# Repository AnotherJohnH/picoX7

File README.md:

# picoX7

A software simulation of the Yamaha DX7 with a USB and physical MIDI interface for the Raspberry Pi Pico

Slightly boring [video](https://youtu.be/ZSuNV67vHK8) of the picoX7 playing the Yamaha DX7 ROM cartridge 1A patches...

## Status

Done...
   + I2S (via PIO) 16-bit stereo DAC interface at 49096 Hz
   + Use of the 2nd Arm Cortex-M, 8 voices per core
   + MIDI in support via UART and USB (including SYSEX in)
   + YM21280 OPS simulation (logarithmic)
   + YM21290 EGS simulation
   + Firmware simulation including pitch envelope, LFO, key sensitivity, level scaling, amplitude modulation
   + DX7 voice patches sounding close

To do...
   - Tune EGS simulation
   - Rate scaling
   - Portamento and glissando
   - Optimise to squeeze in more voices (?)

Limitations...
   - DAC implementation is quite different to the original. Dynamic range might be reduced?
   - Hitachi 6303 (~MC6803) CPU controller and firmware are not being emulated or fully simulated
   - 8 voices are on the left channel and 8 on the right ... stereo output needs to mixed to mono externally

Deviations/enhancements compared to a real DX7...
   + Each voice has it's own LFO
   + Each voice has it's own patch state (in theory when supported could load a different patch into each voice)
   + Support for 128 voice patches (DX7 had 32 internal and 32 cartridge)

See the [software blog](https://github.com/AnotherJohnH/picoX7/wiki/Software-Blog) and [hardware blog](https://github.com/AnotherJohnH/picoX7/wiki/Hardware-Blog)  for more detailed progress updates.

## Hardware

[Schematic](https://github.com/AnotherJohnH/Hardware/blob/main/picoX7/docs/schematic_v0.05.pdf) for the above.

For more information see [README](https://github.com/AnotherJohnH/Hardware/blob/main/picoX7/README.md) and the [hardware blog](https://github.com/AnotherJohnH/picoX7/wiki/Hardware-Blog)

The Pico is significantly overclocked to 191.08 MHz to support 16 voices and generate a jitter free sample rate of 49096 Hz.

RP2350 Picos as well as the older RP2040 Picos are supported.

## Software

### Checkout

This repo uses git sub-modules, so checkout using --recurse to clone all the
dependent source...

    git clone --recurse https://github.com/AnotherJohnH/picoX7.git

or

    git clone --recurse ssh://git@github.com/AnotherJohnH/picoX7.git

### Software dependencies

+ https://github.com/AnotherJohnH/Platform
+ arm-none-eabi-gcc
+ cmake via UNIX make or auto detection of ninja if installed
+ Python3
+ SDL2 (only for native test target)

### Build

Being developed on MacOS but should build on Linux too.

Indirect build of all supported targets, rpipico, rpipico2 and native with cmake and make (or ninja)...

    make

Build a single hardware target e.g. rpipico2 using cmake...

    mkdir build
    cd build
    cmake -DCMAKE_BUILD_TYPE=Release -DPLT_TARGET=rp2350 -DCMAKE_TOOLCHAIN_FILE=Platform/MTL/rp2350/target/toolchain.cmake ..
    make

flashable images will be found under the build sub-directory here...

    build/<target>/picoX7_RPIPIOC_I2S_DAC.uf2
    build/<target>/picoX7_RPIPIOC_PWM_DAC.uf2
    build/<target>/picoX7_RPIPIOC_PIMORONI_PICO_AUDIO.uf2
    build/<target>/picoX7_RPIPIOC_WAVESHARE_REV2_1.uf2
    build/<target>/picoX7_PIMORONI_VGA_DEMO.uf2

Build the native target...

    mkdir build
    cd build
    cmake -DCMAKE_BUILD_TYPE=Release -DPLT_TARGET=native ..
    make

a runable binary image will be found under the build subdirectory here...

    build/Source/picoX7_NATIVE

## License

This project is licensed under the MIT License - see the [LICENSE](LICENSE) file for details

## Acknowledgements

 + [Ken Shirriff](https://github.com/shirriff) for his very helpful series of [blogs](https://www.righto.com/2021/11/reverse-engineering-yamaha-dx7.html) reverse engineering the YM21280
 + [AJXS](https://github.com/ajxs) for their annotated [disassembly](https://ajxs.me/blog/Yamaha_DX7_Firmware_ROM_Disassembly.html) of the DX7 firmware ROM
 + The [Dexed](https://asb2m10.github.io/dexed) developers for providing an easily accessible DX7 audio reference
 + The raspberry-pi foundation for the innovative [RP2040](https://www.raspberrypi.com/documentation/microcontrollers/rp2040.html)
 + The engineers at [Yamaha](https://www.yamaha.com/en/about/design/synapses/id_009)

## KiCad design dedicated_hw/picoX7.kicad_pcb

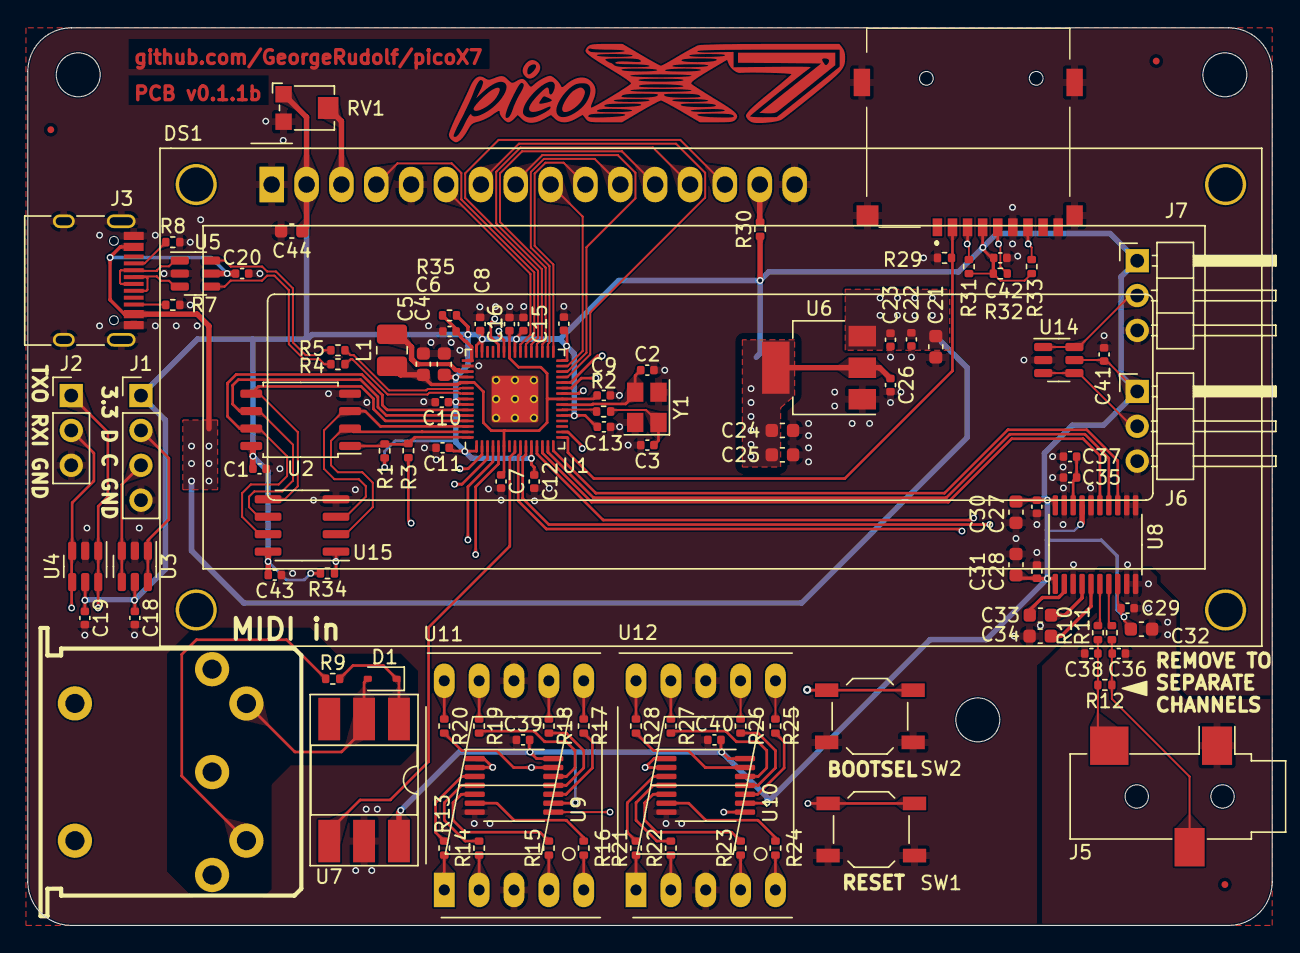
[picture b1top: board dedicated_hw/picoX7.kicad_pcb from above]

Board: 4 copper layers, 90.7 x 65.4 mm, 112 parts (0 on the bottom side), 97 nets.

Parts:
C1, C7, C9, C11, C12, C13, C14, C15, C16, C18, C19, C20, C23, C26, C27, C28, C29, C35, C39, C40, C41, C43: 100nF; C_0402_1005Metric
C2, C3: 22pF; C_0402_1005Metric
C4, C5: 4.7uF; C_0603_1608Metric
C6, C42: 4.7uF; C_0402_1005Metric
C8, C10, C22, C37: 1uF; C_0402_1005Metric
C21, C30, C31, C32: 10uF; C_0603_1608Metric
C24, C25: 22uF; C_0603_1608Metric
C33, C34, C44: 2.2uF; C_0603_1608Metric
C36, C38: 2.2nF; C_0402_1005Metric
D1: 1N4148WS; D_SOD-323
DS1: WC1602A
FID1, FID2, FID3: Fiducial; Fiducial_0.5mm_Mask1mm
H1, H2, H3: MountingHole_3.2mm_M3
J1: Conn_01x04; PinHeader_1x04_P2.54mm_Vertical
J2: Conn_01x03; PinHeader_1x03_P2.54mm_Vertical
J3: USB_DATA; USB_C_Receptacle_HRO_TYPE-C-31-M-12
J4: MIDI in; DIN5-180
J5: PJ-320-3P SMT; PJ-320
J6, J7: Conn_01x03; PinHeader_1x03_P2.54mm_Horizontal
J8: TF003; TF01A
L1: 3.3uH; L_1008_2520Metric_Pad1.43x2.20mm_HandSolder
R1, R34: 4k7; R_0402_1005Metric
R2, R3: 1k; R_0402_1005Metric
R4, R5, R35: 27; R_0402_1005Metric
R7, R8: 5k1; R_0402_1005Metric
R9: 220; R_0402_1005Metric
R10, R11: 470; R_0402_1005Metric
R12: 0; R_0402_1005Metric
R13, R14, R15, R16, R17, R18, R19, R20, R21, R22, R23, R24, R25, R26, R27, R28, R30: 330; R_0402_1005Metric
R29: 1M; R_0402_1005Metric
R31, R32, R33: 10k; R_0402_1005Metric
RV1: 10k; Potentiometer_Bourns_TC33X_Vertical
SW1, SW2: SW_SPST; SW_SPST_TL3342
U1: RP2350A; RP2350-QFN-60-1EP_7x7_P0.4mm_EP3.4x3.4mm_ThermalVias
U2: W25Q128JVS; SOIC-8_5.23x5.23mm_P1.27mm
U3, U4, U5, U14: USB TVS; SOT-23-6
U6: AMS1117-3.3; SOT-223-3_TabPin2
U7: H11L1; DIP-6_W8.89mm_SMDSocket_LongPads
U8: PCM5100A; TSSOP-20_4.4x6.5mm_P0.65mm
U9, U10: 74HC164; TSSOP-14_4.4x5mm_P0.65mm
U11, U12: SM420501N/8; 7SegmentLED_LTS6760_LTS6780
U15: SOIC-8_3.9x4.9mm_P1.27mm
Y1: 12MHz; Crystal_SMD_3225-4Pin_3.2x2.5mm

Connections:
+1V1: C5.1, C7.1, C8.1, C9.1, L1.1, U1.6 (DVDD), U1.23 (DVDD), U1.39 (DVDD), U1.50 (VREG_FB)
+3V3: C1.1, C4.1, C10.1, C11.1, C12.1, C13.1, C14.1, C15.1, C16.1, C18.1, C19.1, C24.1, C25.1, C26.1, C27.1, C28.1, C29.1, C30.1, C31.1, C32.1, C39.1, C40.1, C41.1, C42.1, C43.1, C44.1, DS1.2 (VDD), J1.1, J6.1, J7.1, J8.4 (VDD), R1.2, R30.1, R31.2, R32.2, R33.2, R34.2, R35.2, RV1.1, U1.1 (IOVDD), U1.11 (IOVDD), U1.20 (IOVDD), U1.30 (IOVDD), U1.38 (IOVDD), U1.44 (ADC_AVDD), U1.45 (IOVDD), U1.49 (VREG_VIN), U1.53 (USB_OTP_VDD), U1.54 (QSPI_IOVDD), U2.8 (VCC), U3.5 (VBUS), U4.5 (VBUS), U6.2 (VO), U7.6, U8.1 (CPVDD), U8.8 (AVDD), U8.17 (XSMT), U8.20 (DVDD), U9.9 (~MR), U9.14 (VCC), U10.9 (~MR), U10.14 (VCC), U14.5 (VBUS), U15.8 (VCC)
+5V: C20.1, C21.1, C22.1, C23.1, J3.A4 (VBUS), J3.A9 (VBUS), J3.B4 (VBUS), J3.B9 (VBUS), U5.5 (VBUS), U6.3 (VI)
/Audio Output/I2S_CLK: U1.13 (GPIO9), U8.15 (LRCK)
/Audio Output/I2S_DAT: U1.14 (GPIO10), U8.14 (DIN)
/Audio Output/I2S_LRCLK: U1.15 (GPIO11), U8.13 (BCK)
/Audio Output/L_CH: C38.1, J5.T, R10.2, R12.2
/Audio Output/R_CH: C36.1, J5.R, R11.2, R12.1
/BOOTSEL: R3.2, SW2.2 (B)
/DEBUG_RXI: J2.2, U1.3 (GPIO1), U4.3 (I/O2), U4.4 (I/O2)
/DEBUG_TXO: J2.1, U1.2 (GPIO0), U4.1 (I/O1), U4.6 (I/O1)
/MIDI: U1.8 (GPIO5), U7.4
/RP2350 Core/7SEG_SEGDAT: U1.4 (GPIO2), U9.1 (DSA), U9.2 (DSB)
/RP2350 Core/7SEG_SHFCLK: U1.5 (GPIO3), U9.8 (CP), U10.8 (CP)
/RP2350 Core/ADC0: J6.2, U1.40 (GPIO26_ADC0), U14.3 (I/O2), U14.4 (I/O2)
/RP2350 Core/ADC1: J7.2, U1.41 (GPIO27_ADC1), U14.1 (I/O1), U14.6 (I/O1)
/RP2350 Core/DISP_D0: DS1.7 (D0), U1.27 (GPIO16)
/RP2350 Core/DISP_D1: DS1.8 (D1), U1.28 (GPIO17)
/RP2350 Core/DISP_D2: DS1.9 (D2), U1.29 (GPIO18)
/RP2350 Core/DISP_D3: DS1.10 (D3), U1.31 (GPIO19)
/RP2350 Core/DISP_D4: DS1.11 (D4), U1.32 (GPIO20)
/RP2350 Core/DISP_D5: DS1.12 (D5), U1.33 (GPIO21)
/RP2350 Core/DISP_D6: DS1.13 (D6), U1.34 (GPIO22)
/RP2350 Core/DISP_D7: DS1.14 (D7), U1.35 (GPIO23)
/RP2350 Core/DISP_E: DS1.6 (E), U1.37 (GPIO25)
/RP2350 Core/DISP_RS: DS1.4 (RS), U1.36 (GPIO24)
/RP2350 Core/QSPI_SCLK: U1.56 (QSPI_SCLK), U2.6 (CLK), U15.6 (CLK)
/RP2350 Core/QSPI_SD0: U1.57 (QSPI_SD0), U2.5 (DI(IO0)), U15.5 (DI(IO0))
/RP2350 Core/QSPI_SD1: U1.59 (QSPI_SD1), U2.2 (DO(IO1)), U15.2 (DO(IO1))
/RP2350 Core/QSPI_SD2: U1.58 (QSPI_SD2), U2.3 (IO2), U15.3 (IO2)
/RP2350 Core/QSPI_SD3: U1.55 (QSPI_SD3), U2.7 (IO3), U15.7 (IO3)
/RP2350 Core/SD_CLK: J8.5 (CLK), R32.1, U1.12 (GPIO8)
/RP2350 Core/SD_MISO: J8.7 (DAT0/DO), R33.1, U1.10 (GPIO7)
/RP2350 Core/SD_MOSI: J8.3 (CMD/DI), R31.1, U1.9 (GPIO6)
/RP2350 Core/USB_D+: R4.2, U1.52 (USB_DP)
/RP2350 Core/USB_D-: R5.2, U1.51 (USB_DM)
/RP2350 Core/VREG_LX: L1.2, U1.48 (VREG_LX)
/RP2350 Core/XIN: R2.1, U1.21 (XIN)
/RP2350 Core/XOUT: C2.1, U1.22 (XOUT), Y1.3
/RP2350 Core/~QSPI_SS: R1.1, R3.1, U1.60 (QSPI_SS), U2.1 (~CS)
/RP2350 Core/~SD_CS: J8.2 (DAT3/CS), R29.2, U1.16 (GPIO12)
/RP2350 Core/~SPARE_SS: R34.1, U1.17 (GPIO13), U15.1 (~CS)
/RUN: SW1.2 (B), U1.26 (RUN)
/SWCLK: J1.3, U1.24 (SWCLK), U3.3 (I/O2), U3.4 (I/O2)
/SWDAT: J1.2, U1.25 (SWD), U3.1 (I/O1), U3.6 (I/O1)
/USB+: R4.1, U5.4 (I/O2)
/USB, Power, IO/CC1: J3.A5 (CC1), R8.1
/USB, Power, IO/CC2: J3.B5 (CC2), R7.1
/USB, Power, IO/Din+: J3.A6 (D+), J3.B6 (D+), U5.3 (I/O2)
/USB, Power, IO/Din-: J3.A7 (D-), J3.B7 (D-), U5.1 (I/O1)
/USB-: R5.1, U5.6 (I/O1)
/User Interface/A1: R18.1, U11.7 (A)
/User Interface/A2: R26.1, U12.7 (A)
/User Interface/B1: R17.1, U11.6 (B)
/User Interface/B2: R25.1, U12.6 (B)
/User Interface/C1: R15.1, U11.4 (C)
/User Interface/C2: R23.1, U12.4 (C)
/User Interface/D1: R14.1, U11.2 (D)
/User Interface/D2: R22.1, U12.2 (D)
/User Interface/DP1: R16.1, U11.5 (DP)
/User Interface/DP2: R24.1, U12.5 (DP)
/User Interface/E1: R13.1, U11.1 (E)
/User Interface/E2: R21.1, U12.1 (E)
/User Interface/F1: R19.1, U11.9 (F)
/User Interface/F2: R27.1, U12.9 (F)
/User Interface/G1: R20.1, U11.10 (G)
/User Interface/G2: R28.1, U12.10 (G)
GND: C1.2, C2.2, C3.2, C4.2, C5.2, C6.2, C7.2, C8.2, C9.2, C10.2, C11.2, C12.2, C13.2, C14.2, C15.2, C16.2, C18.2, C19.2, C20.2, C21.2, C22.2, C23.2, C24.2, C25.2, C26.2, C27.2, C28.2, C29.2, C30.2, C31.2, C32.2, C34.2, C35.2, C36.2, C37.2, C38.2, C39.2, C40.2, C41.2, C42.2, C43.2, C44.2, DS1.1 (VSS), DS1.5 (R/W), DS1.16 (LED(-)), J1.4, J2.3, J3.A1 (GND), J3.A12 (GND), J3.B1 (GND), J3.B12 (GND), J3.S1 (SHIELD), J5.S, J6.3, J7.3, J8.6 (GND), J8.CD1, J8.MP1, J8.MP2, J8.MP3, J8.MP4, R7.2, R8.2, R29.1, RV1.3, SW1.1 (A), SW2.1 (A), U1.47 (VREG_PGND), U1.61 (GND), U2.4 (GND), U3.2 (GND), U4.2 (GND), U5.2 (GND), U6.1 (GND), U7.5, U8.3 (CPGND), U8.9 (AGND), U8.10 (DEMP), U8.11 (FLT), U8.12 (SCK), U8.16 (FMT), U8.19 (DGND), U9.7 (GND), U10.7 (GND), U11.3 (CC), U11.8 (CC), U12.3 (CC), U12.8 (CC), U14.2 (GND), U15.4 (GND), Y1.2, Y1.4
unnamed: C3.1, R2.2, Y1.1
unnamed: D1.2 (A), J4.5, U7.2
unnamed: D1.1 (K), R9.1, U7.1
unnamed: DS1.15 (LED(+)), R30.2
unnamed: DS1.3 (VO), RV1.2
unnamed: J4.4, R9.2
unnamed: C6.1, R35.1, U1.46 (VREG_AVDD)
unnamed: C33.2, U8.4 (CAPM)
unnamed: C33.1, U8.2 (CAPP)
unnamed: C35.1, C37.1, U8.18 (LDOO)
unnamed: R10.1, U8.6 (OUTL)
unnamed: R11.1, U8.7 (OUTR)
unnamed: C34.1, U8.5 (VNEG)
unnamed: R13.2, U9.3 (Q0)
unnamed: R14.2, U9.4 (Q1)
unnamed: R15.2, U9.5 (Q2)
unnamed: R16.2, U9.6 (Q3)
unnamed: R17.2, U9.10 (Q4)
unnamed: R18.2, U9.11 (Q5)
unnamed: R19.2, U9.12 (Q6)
unnamed: R20.2, U9.13 (Q7), U10.1 (DSA), U10.2 (DSB)
unnamed: R21.2, U10.3 (Q0)
unnamed: R22.2, U10.4 (Q1)
unnamed: R23.2, U10.5 (Q2)
unnamed: R24.2, U10.6 (Q3)
unnamed: R25.2, U10.10 (Q4)
unnamed: R26.2, U10.11 (Q5)
unnamed: R27.2, U10.12 (Q6)
unnamed: R28.2, U10.13 (Q7)

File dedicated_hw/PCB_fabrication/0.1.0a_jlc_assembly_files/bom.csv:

Designator,Footprint,Quantity,Value,LCSC Part #
"C1, C11, C12, C13, C14, C15, C16, C18, C19, C20, C23, C26, C27, C28, C29, C35, C39, C40, C41, C42, C43, C6, C7, C9",402,24,100nF,C307331
"C10, C22, C37, C8",402,4,1uF,C52923
C17,402,1,4.7nF,C1538
"C2, C3",402,2,22pF,C1555
"C21, C30, C31, C32",603,4,10uF,C96446
"C24, C25",603,2,22uF,C59461
"C33, C34, C44",603,3,2.2uF,C23630
"C36, C38",402,2,2.2nF,C1531
"C4, C5",402,2,4.7uF,C23733
D1,D_SOD-323,1,1N4148WS,C2128
DS1,WC1602A,1,WC1602A,C5329588
J3,USB_C_Receptacle_HRO_TYPE-C-31-M-12,1,USB_DATA,C165948
J4,DIN5-180,1,MIDI in,C2939344
J5,PJ-320,1,PJ-320-3P SMT,C17701688
J8,TF01A,1,TF003,C91145
L1,1008,1,3.3uH,C222831
"R1, R34",402,2,4k7,C25905
"R10, R11",402,2,470,C25117
R12,402,1,0,C21376
"R13, R14, R15, R16, R17, R18, R19, R20, R21, R22, R23, R24, R25, R26, R27, R28, R30",402,17,330,C25104
"R2, R3",402,2,1k,C11702
"R29, R6",402,2,1M,C26083
"R4, R5",402,2,27,C25092
"R7, R8",402,2,5k1,C25905
R9,402,1,220,C25091
RV1,Potentiometer_Bourns_TC33X_Vertical,1,10k,C719176
"SW1, SW2",SW_SPST_TL3342,2,SW_SPST,C318884
U1,RP2350-QFN-60-1EP_7x7_P0.4mm_EP3.4x3.4mm_ThermalVias,1,RP2350A,C42411118
"U10, U9",TSSOP-14_4.4x5mm_P0.65mm,2,74HC164,C5612
"U11, U12",7SegmentLED_LTS6760_LTS6780,2,SM420501N/8,C252201
"U14, U3, U4, U5",SOT-23-6,4,USB TVS,C2827654
U2,SOIC-8_5.23x5.23mm_P1.27mm,1,W25Q128JVS,C97521
U6,SOT-223-3_TabPin2,1,AMS1117-3.3,C6186
U7,DIP-6_W8.89mm_SMDSocket_LongPads,1,H11L1,C20612622
U8,TSSOP-20_4.4x6.5mm_P0.65mm,1,PCM5100A,C131154
Y1,Crystal_SMD_3225-4Pin_3.2x2.5mm,1,12MHz,C133334

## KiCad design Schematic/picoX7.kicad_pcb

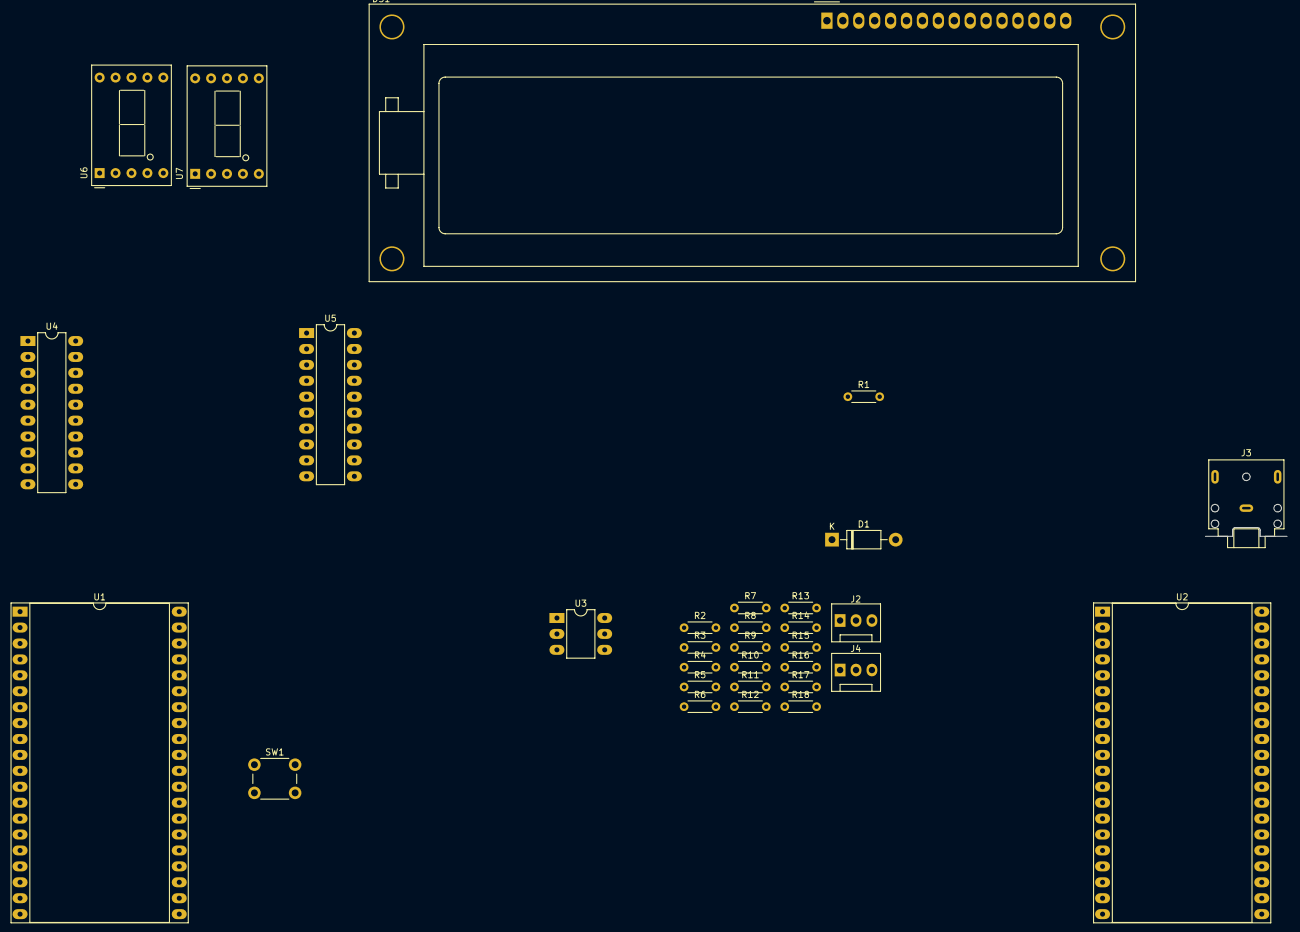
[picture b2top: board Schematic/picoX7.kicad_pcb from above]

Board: 2 copper layers, 31 parts (0 on the bottom side), 43 nets, no tracks yet.

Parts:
D1: 1N4001; D_DO-41_SOD81_P10.16mm_Horizontal
DS1: HY1602E
J2, J4: Debug; FanPinHeader_1x03_P2.54mm_Vertical
J3: Stereo line out; Jack_3.5mm_CUI_SJ1-3523N_Horizontal
R1: 220; R_Axial_DIN0204_L3.6mm_D1.6mm_P5.08mm_Horizontal
R2: 1K; R_Axial_DIN0204_L3.6mm_D1.6mm_P5.08mm_Horizontal
R3, R4, R5, R6, R7, R8, R9, R10, R11, R12, R13, R14, R15, R16, R17, R18: 330; R_Axial_DIN0204_L3.6mm_D1.6mm_P5.08mm_Horizontal
SW1: RST; SW_PUSH_6mm_H5mm
U1: MCU arm Cortex-M0x2; DIP-40_W25.4mm_Socket_LongPads
U2: I2S DAC; DIP-40_W25.4mm_Socket_LongPads
U3: H11L1; DIP-6_W7.62mm_LongPads
U4, U5: 74HCT374; DIP-20_W7.62mm_LongPads
U6, U7: D1X8K-14BL; D1X8K

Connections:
+3V3: U1.36 (3V3), U3.6, U4.20 (VCC), U5.20 (VCC)
+5V: DS1.2 (LEDA), DS1.4 (VDD), R2.2, U1.40 (VBUS)
/1.571072 MHz: U1.34 (GPIO28_ADC2), U2.34 (SCLK)
/12.568576 MHz: U1.31 (GPIO26_ADC0), U2.31 (MCLK)
/49.096 KHz: U1.32 (GPIO27_ADC1), U2.32 (LRCLK)
/31250 baud 8-N-1: U1.7 (GPIO5), U3.4
/D0: DS1.9 (DB0), U1.9 (GPIO6), U4.3 (D0), U5.3 (D0)
/D1: DS1.10 (DB1), U1.10 (GPIO7), U4.4 (D1), U5.4 (D1)
/D2: DS1.11 (DB2), U1.11 (GPIO8), U4.7 (D2), U5.7 (D2)
/D3: DS1.12 (DB3), U1.12 (GPIO9), U4.8 (D3), U5.8 (D3)
/D4: DS1.13 (DB4), U1.14 (GPIO10), U4.13 (D4), U5.13 (D4)
/D5: DS1.14 (DB5), U1.15 (GPIO11), U4.14 (D5), U5.14 (D5)
/D6: DS1.15 (DB6), U1.16 (GPIO12), U4.17 (D6), U5.17 (D6)
/D7: DS1.16 (DB7), U1.17 (GPIO13), U4.18 (D7), U5.18 (D7)
/I2S SD: U1.29 (GPIO22), U2.29 (DIN)
/MIDI in (RX) 115200 baud 8-N-1: J2.2, U1.2 (GPIO1)
/console (TX) 115200 baud 8-N-1: J2.1, U1.1 (GPIO0)
Earth: DS1.1 (LEDK), DS1.3 (VSS), DS1.7 (R/~W), SW1.2, U1.38 (GND), U2.3 (GND), U2.8 (GND), U2.13 (GND), U2.18 (GND), U2.23 (GND), U2.28 (GND), U2.33 (GND), U2.38 (GND), U3.5, U4.1 (OE), U4.10 (GND), U5.1 (OE), U5.10 (GND), U6.3 (CC), U6.8 (CC), U7.3 (CC), U7.8 (CC)
unnamed: D1.2 (A), U3.2
unnamed: D1.1 (K), R1.1, U3.1
unnamed: DS1.8 (E), U1.20 (GPIO15)
unnamed: DS1.6 (RS), U1.19 (GPIO14)
unnamed: J2.3, U1.3 (GND)
unnamed: U1.4 (GPIO2), U5.11 (Cp)
unnamed: U1.5 (GPIO3), U4.11 (Cp)
unnamed: SW1.1, U1.30 (RUN)
unnamed: U1.39 (VSYS), U2.39 (VSYS)
unnamed: R3.1, U6.7 (A)
unnamed: R4.1, U6.6 (B)
unnamed: R5.1, U6.4 (C)
unnamed: R6.1, U6.2 (D)
unnamed: R10.1, U6.5 (DP)
unnamed: R7.1, U6.1 (E)
unnamed: R8.1, U6.9 (F)
unnamed: R9.1, U6.10 (G)
unnamed: R11.1, U7.7 (A)
unnamed: R12.1, U7.6 (B)
unnamed: R13.1, U7.4 (C)
unnamed: R14.1, U7.2 (D)
unnamed: R18.1, U7.5 (DP)
unnamed: R15.1, U7.1 (E)
unnamed: R16.1, U7.9 (F)
unnamed: R17.1, U7.10 (G)

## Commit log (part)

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2023-06-11 Initial
2023-06-12 Add Usage
2023-06-12 Update to PIO I2S driver to fix SD alignment
2023-06-13 A440 sine wave generator
2023-06-17 Some source restructure
2023-06-18 Working polyphonic synth with Simple voice - mbedLPC1768 and native targets broken XXX
2023-06-18 Rework to allow mbedLPC1768 and nativew builds
2023-06-21 Add DX7 initial
2023-06-26 Rename project and minor doc update
2023-06-27 Some DX7 improvements mainly exposing the program rom data to the voice class
2023-06-27 Dynamic algorithm
2023-07-01 Start to add EG support
2023-07-02 Small class refactor
2023-07-02 Ratio frequency calcs corrected
2023-07-03 Some DX7 fidelity fixes - still a long way off
2023-07-04 DX7: Add some detune
2023-07-04 DX7: OP output level
2023-07-04 Tidy source
2023-07-05 Code tidy and README updates
2023-07-05 Some minor main program updates
2023-07-05 Update version
2023-07-05 Spelling
2023-07-06 Prepare for pitch EG
2023-07-07 Provide access to all four factory ROM cartridges
2023-07-07 Pitch bend does
2023-07-09 Initial LFO implementation
2023-07-09 Some refactoring of DX7 Voice
2023-07-09 Minor factual correction
2023-07-13 SysEx type refactoring for unpacked voice
2023-07-13 Tune EGS
2023-07-13 Add bread board snap
2023-07-13 Some SysEx initialisation
2023-07-13 Switch voice programming to unpacked SysEx structure
2023-07-14 Keep Yamaha ROM images seperate for clearer IP ownership
2023-07-14 Some SYSEX improvements
2023-07-15 Better MIDI channel mode support in particular "All Sounds Off"
2023-07-15 Improve porogram sweep test
2023-07-16 Avoid a warning with gcc 11
2023-07-16 Some minor type corrections in the audio path
2023-07-17 Update UART implementation for more reliable debug and MIDI comms
2023-07-17 Overclocked to 191MHz to achieve 8 voices at 49096Hz - now seems more reliable now the UARTs are buffered
2023-07-20 Add a file header
2023-07-20 Add MC6803 instruction set doc
2023-07-22 Sysex debug updates
2023-07-23 Firmware research progress
2023-07-23 Some LFO updates
2023-07-23 Avoid missing vfprintf() in Platform
2023-07-23 Fix Linux build bug
2023-07-23 Add transpose
2023-07-23 Reformat SysEx dump along the lines of Yamaha's original patch form
2023-07-24 Research updates
2023-07-28 Minor voice updates - nothing significant
2023-07-28 Tidy up Python a test driver
2023-07-29 Add start of MIDI file decoder
2023-07-30 Update console baud (via Platform updatye) to 115200
2023-07-30 Cut back to 6 voice at 191 MHz for now - seems to solve audio glitches and occasional crash
2023-07-30 Add MIDI program override to player
2023-07-30 MIDI meta commands contain their size!
2023-07-30 Intercept meta events in the MIDI player
2023-07-31 Some tidy up of the MIDI Python code
2023-07-31 Split Egs and Ops implementation into seperate classes
2023-07-31 Add Firmware class as a place to model the DX7 firmware
2023-08-01 Correct some mistakes in the EGS chart
2023-08-01 Replace Reseacrh makefile with a cmake file
2023-08-01 Rename Test dir as Demo so that a proper Test directory can be setup
2023-08-01 Add a simple EGS test (exerciser)
2023-08-01 Move some implementation for DX7/Voice into Firmware
2023-08-02 Replace note frequency caclulation with algorithm from firmware
2023-08-02 Some YM21280 diagram updates
2023-08-02 Some firmware and MIDI fraemwork updates
2023-08-03 Clear debug console on startup
2023-08-04 Add log-sine png for wiki = Also add auto-generation for use in C++ OPS model
2023-08-04 Add exp plot pngs for wiki
2023-08-05 Preparing to switch OPS to a logarithmic implementation
2023-08-28 Add schematic files (KiCad)
2023-08-30 Update schematic with planned extensions
2023-09-03 Add 7-segment display of current program number
2023-09-03 Update schematic to reflect changes to LED display
2023-09-05 Minor schematic update
2023-09-07 Update Platform for improved timer support
2023-09-09 Refactor docs directories
2023-09-09 Update breadboard photos
2023-09-09 Add ADC slider input
2023-09-16 Update README.md
    Better Yamaha link credit
2023-09-18 Add more of the Yamaha voice rom Sysex dumps
2023-09-24 Some minor updates to the EGS research
2023-09-30 Re-sync the C++ translations after the previouis update
2023-10-01 Update EGS diagram with updated labels from AJXS
2024-02-23 Move python helper scripts into Platform
2024-06-05 Add build support for multiple hardware targets
2024-06-05 Add build support for PiMoroni VGA demo board
2024-06-05 Add "any voice on debug" via on-board LED
2024-06-05 Route console debug via the MIDI uart for Pimoroni VGA board
2024-06-07 Add support for I2C LCD Note: Implementation in Platform is not working yet
2024-06-07 Add HW description to debug console banner
2024-06-17 Now appears as a USB device - non-functional
2024-06-17 Some USB device updates - still non-functional
2024-06-21 Tidy away some debug printf
2024-06-21 Fix mis-decode of USB MIDI packets
2024-06-22 Some tidy and refactor of the USB device implementation
2024-06-29 Rework Synth and Voice base classes
2024-07-06 Common source code for Pico and native builds
2024-07-06 Move profiling reporting to LCD and 7-seg LED
2024-07-06 Minor tidy
2024-07-06 Refactor Egs/Ops implementation for a few % perf improvement
2024-07-06 Remove bisassembly
2024-07-06 Add MIDI in to native test build
2024-07-07 Tidy EnvGen class + Possiblky faster on more complex microarchitecture but no faster for me on Cortex-M0!
2024-07-07 Move synth tick into the main thread out of the audio IRQ handler + seems to avoid some audio glitches
2024-07-08 Get samples 2 at a time for a small performance gain
2024-07-09 Fix unterminated string bug that broke patch SysEx
2024-07-10 Platform update to fix broken mono I2S
2024-07-13 Share voice rendering between the two cores
2024-07-15 Mess with priorities
2024-07-15 Revert "Mess with priorities"
    This reverts commit f66653e9f8f281f31c0032304f51b6ec10332f69.
2024-07-19 Update Platform as an attempt to fix the cacaphonic crash
    - May have been DMA channel overrun
2024-07-22 Re-implement EGS rate calculations
2024-07-24 Some changes to EGS levels
2024-09-08 Update Platform to support I2C 16x2 LCD
2024-09-08 Build support for Raspberry Pi Pico2 builds but not working yet
2024-09-09 Build on GitHub Actions
2024-09-09 Build all pushes
2024-09-09 Document native build
2024-09-09 Update Platform for some Linux MIDI support
2024-09-15 Revert last change
2024-09-15 Update Platform
2024-09-15 Pimoroni pico audio support working
2024-09-15 Raspberry Pi Pico 2 support working
2024-09-29 Add PWM audio support ...
    + Sounds quality, as may well be expected, is "poor". But does
    allow for a basic implementation using just a Pico and a few
    resistors and capacitors (i.e. no external DAC required)
2024-09-29 Clearer I2C LCD address configuration
2024-10-01 Updated schematic
2024-10-01 Speculate support for back-pack I2C LCD
    For Waveshare DAC with I2C LCD use the alternate
    AlphaNumLcd class with I2C address 0x27
2024-11-17 Split hardware interface configuartion out of picoX7.cpp for easier navigation and re-use
2024-11-17 Docs update
2024-12-29 Make MIDI debug easier to configure
2024-12-29 Update Platform and fix Waveshare I2S DAC integration
2025-01-03 Update Platform URL to ssh
2025-01-12 Fix missing MIDI rx pull-up in software
    Thanks sysop8866 for noticing and reporting!
    NOTE: This patch also includes a significant update to
    Platform
2025-01-12 gitignore update and Linux build fix
2025-01-19 Update Platform to help fix MIDI SYSEX programming
2025-01-21 Fix for operator level quantization bug
    + for improved sound
2025-02-07 Remove Ableton Live set as no longer useful
    - Also contained a dodgy filename that some OSes struggled to
    cope with
2025-02-07 Re-code modulation source code
2025-02-09 Modulation sources corrections and tidy
2025-02-11 Updates for Lfo, and pitch EG
    - Not complete
2025-02-12 Add an EnvGen test
2025-02-12 EnvGen re-write
2025-02-12 Temporary fix for broken pitch mod
2025-02-14 Some firmware emulation updates
2025-02-15 Add some EGS register debug for HW_NATIVE builds
2025-02-15 Re-route EGS freq send to OPS
2025-02-15 Pitch modulation fix
2025-02-16 Some fixes for voice frequency
2025-02-16 Fix for recently broken single voice SysEx download
2025-02-16 Fix LFO waveforms
2025-02-17 Fix for PitchEG
2025-02-17 Fix for modulation crash
2025-02-17 Tidy Sysex patch size constants
2025-02-17 Fix register simulation for op level
2025-02-20 Add comments for fake midi messages
2025-02-20 Add conversion of MIDI velocity to internal representation
2025-02-20 Fixes for keyboard scaling OP level calcs
    Note: These more accurate values are still
    not used in the sound EGS simulation
2025-02-20 Disable EGS register simulation debug for now
    + Values for "BRASS 1" now match those from emulating the
    real firmware
2025-02-21 Switch to accurate scaled op levels
2025-02-22 Initial attempt at using log sine table
2025-02-22 Fix for recent fixed op frequecy regression
2025-02-22 Improve fidelity og amp EG now log wavetable is in use
2025-02-22 Stop throwing away modulation bits in the OPS
2025-02-24 Update README.md for recent sound improvements
2025-02-24 Cosmetic tidy no functional change
2025-02-24 Fix first 8 notes played are bad bug!
2025-02-24 Some frequency limit fixes
2025-02-24 Invert x scale in exp_14 func to avoid a runtime subtraction
2025-02-24 Add full program number to display and remove redundant INT/CRT
2025-02-24 Modernize active patch display
    - Exact replication of DX7 display was not adding much
    + Now with MIDI program number from 1-128, algorithm, feedback
    and op fixed/ratio state
2025-02-26 Pointless tidy of AUTO.py
2025-02-26 Fix for amplitude EG level scaling
2025-02-28 Update README video link to fresh recording
2025-02-28 Minor fix to console output
2025-03-04 Make EnvGen easier to explore in a test harness
2025-03-04 Tidy EGS level calcs to use a more likely number of bits
2025-03-04 Not sure how many bits OPS modulation value should be but 12 seems to low
2025-03-04 Fix some compiler warnings found with gcc-13
2025-03-04 Source tidy
2025-03-05 Remove dependency of Ops on EnvGen to make unit testing easier
2025-03-06 Add initial OPS test
2025-03-06 Minor test cmake tidy
2025-03-06 Tidy and improve OPS test
2025-03-06 Extend OPS frequency test and fix a potential freq bug
2025-03-07 Fix for low frequencies in the Ops
    The F14 to the OPS can underflow by 0xC00 so that values
    0x3400-0x3FFF are actually negative indexes int the top
    end of the table shifted right by 16 bits
2025-03-07 Initial OPS attenuation test
2025-03-09 Important fix for EGS=>OPS attenuation issue
    - 12-bit attenuation from EGS to OPS was scaled
    incorrectly leading to inaccuracy and ugly
    limit checks
    + EGS and OPS code now corrected
2025-03-09 Some comments
2025-03-09 Cosmetic tidy of EnvGen
2025-03-10 Slowly sorting out 0.1.0 bugs
2025-03-11 Egs tidy
    = should be no functional change
2025-03-11 Some minor identifier name changes
2025-03-12 Remove burotted demo directory
2025-04-12 CMake refactor
2025-04-12 Small cosmetic improvement
2025-04-16 Comment typo
2025-04-16 Update hardware configs - Drop GPIO LCD support + Add general I2S config + Pin assignments moved to be more compatible with picoX21H project
2025-05-22 Update Platform for USB updates
2025-05-25 Fix for MIDI in and I2C LCD out on RP2350
    + Fixes are in Platform
2025-06-06 Re-work autogeneration
2025-06-06 hw updated to bring in picoChippy changes
2025-06-08 Some HW config improvements
2025-06-09 More HW updates
2025-10-10 Platform update
2025-10-10 Shrink license header
2025-10-18 Add Hardware submodule (not used yet)
2025-10-18 Switch to Hardware submodule
2025-10-19 Update Hardware
2025-10-20 Furtrher Hardware update
2025-11-02 Move hardware docs out into Hardware submodule
2025-11-02 Fix console escape sequence
2025-11-09 Update Hardware for better native component simulation
    Also improved support fior AKAI MPKmini controller
    which sends program changes on channel #2
2025-11-22 16 note polyphony
    - Turns out storing lookup tbales in the FLASH was
    causing really significant performance issues
2025-11-27 Minor cosmetic changes
